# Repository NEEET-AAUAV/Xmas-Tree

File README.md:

# :christmas_tree: :santa: :christmas_tree: DETI X-mas Tree :christmas_tree: :santa: :christmas_tree:

A **simple** (yet rather cool!) Christmas Tree using LEDs and Printed Circuit Boards.

## :gift: List of Material
:snowflake: 64 (or 128) LEDs (_preferably 5mm LEDs_)  
:snowflake: 1 Arduino Nano  
:snowflake: 24 BC557  
:snowflake: 4 JHC138 (or 74HCT138)  
:snowflake: SMD Resistors  
:snowflake: Double Layer Printed Circuit Boards  

## :triangular_ruler: Tree Dimensions
:snowflake:  Approximately an A4 paper sheet

## What we did...
:snowflake: [Arduino Code](Xmas_tree.ino/)  
:snowflake: [Schematic & Board](PCB)  
:snowflake: 3D printed parts: [The Original](https://www.thingiverse.com/thing:537944) and [Our version](https://github.com/NEEET-AAUAV/Xmas-Tree/tree/master/Support)

## How we did it?
The projected electrical circuit is similar to a LED matrix, allowing only one LED ON at any given time.   
To create the illusion of multiple LEDs on, the control algorithm toggles the desired LEDs, one by one, through the decoder hardware at a high frequency, therefore creating the illusion of multiple LEDs being on at the same time.  
A decoder IC is required to control the LEDs independently, enabling the creation of multiple and elaborated animation schemes.  

## Authors
:santa: [André Gradim](https://github.com/a-gradim)  
:santa: [Pedro Martins](https://github.com/k3rn3l-pan1c)  

### Other Elfs worth mention
:snowman: [Hugo Leal](https://github.com/HugoLeal)  
:snowman: [Beatriz Silva](https://github.com/b-dsilva)

--- 

Wanna get in contact?  
Reach us by email: neeetua@gmail.com

---

Created By [NEEET - Núcleo de Estudantes de Eletrónica e Telecomunicações](https://www.facebook.com/neeetaauav/)  
[Department of Electronics, Telecommunications and Informatics](https://www.ua.pt/deti/)  
[University of Aveiro](https://www.ua.pt/)

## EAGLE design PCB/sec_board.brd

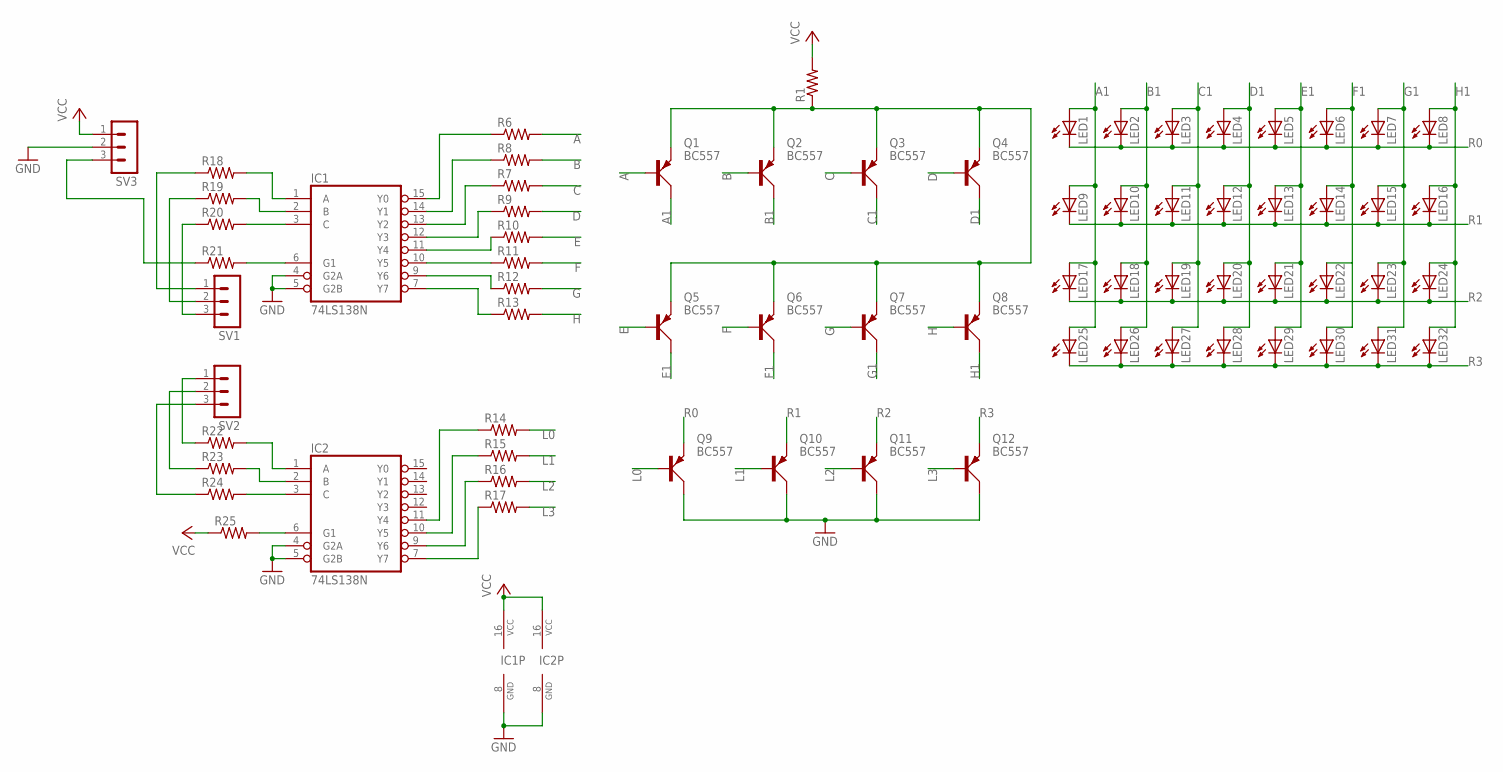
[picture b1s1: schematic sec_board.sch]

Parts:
IC1, IC2: 74LS138N; DIL16
LED1, LED2, LED3, LED4, LED5, LED6, LED7, LED8, LED9, LED10, LED11, LED12, LED13, LED14, LED15, LED16, LED17, LED18, LED19, LED20, LED21, LED22, LED23, LED24, LED25, LED26, LED27, LED28, LED29, LED30, LED31, LED32: LED5MM
Q1, Q2, Q3, Q4, Q5, Q6, Q7, Q8, Q9, Q10, Q11, Q12: BC557; SOT54A
R1, R6, R7, R8, R9, R10, R11, R12, R13, R14, R15, R16, R17: R-US_R0805; R0805
R18, R19, R20, R21, R22, R23, R24, R25: R-US_M0805; M0805
SV1, SV2, SV3: MA03-1

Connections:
A: Q1.B, R6.2
A1: LED1.A, LED9.A, LED17.A, LED25.A, Q1.C
B: Q2.B, R8.2
B1: LED2.A, LED10.A, LED18.A, LED26.A, Q2.C
C: Q3.B, R7.2
C1: LED3.A, LED11.A, LED19.A, LED27.A, Q3.C
D: Q4.B, R9.2
D1: LED4.A, LED12.A, LED20.A, LED28.A, Q4.C
E: Q5.B, R10.2
E1: LED5.A, LED13.A, LED21.A, LED29.A, Q5.C
F: Q6.B, R11.2
F1: LED6.A, LED14.A, LED22.A, LED30.A, Q6.C
G: Q7.B, R12.2
G1: LED7.A, LED15.A, LED23.A, LED31.A, Q7.C
GND: IC1.4 (G2A), IC1.5 (G2B), IC1.8 (GND), IC2.4 (G2A), IC2.5 (G2B), IC2.8 (GND), Q9.C, Q10.C, Q11.C, Q12.C, SV3.2
H: Q8.B, R13.2
H1: LED8.A, LED16.A, LED24.A, LED32.A, Q8.C
L0: Q9.B, R14.2
L1: Q10.B, R15.2
L2: Q11.B, R16.2
L3: Q12.B, R17.2
unnamed: IC2.7 (Y7), R17.1
unnamed: IC1.15 (Y0), R6.1
unnamed: IC1.14 (Y1), R8.1
unnamed: IC2.9 (Y6), R16.1
unnamed: IC1.13 (Y2), R7.1
unnamed: IC1.12 (Y3), R9.1
unnamed: IC1.11 (Y4), R10.1
unnamed: IC1.10 (Y5), R11.1
unnamed: IC1.9 (Y6), R12.1
unnamed: IC1.7 (Y7), R13.1
unnamed: IC2.10 (Y5), R15.1
unnamed: IC2.11 (Y4), R14.1
unnamed: Q1.E, Q2.E, Q3.E, Q4.E, Q5.E, Q6.E, Q7.E, Q8.E, R1.1
unnamed: R24.1, SV2.3
unnamed: R23.1, SV2.2
unnamed: R22.1, SV2.1
unnamed: R20.1, SV1.3
unnamed: R19.1, SV1.2
unnamed: R18.1, SV1.1
unnamed: R21.1, SV3.3
unnamed: IC2.3 (C), R24.2
unnamed: IC2.2 (B), R23.2
unnamed: IC2.1 (A), R22.2
unnamed: IC1.3 (C), R20.2
unnamed: IC1.2 (B), R19.2
unnamed: IC1.1 (A), R18.2
unnamed: IC1.6 (G1), R21.2
unnamed: IC2.6 (G1), R25.2
R0: LED1.K (C), LED2.K (C), LED3.K (C), LED4.K (C), LED5.K (C), LED6.K (C), LED7.K (C), LED8.K (C), Q9.E
R1: LED9.K (C), LED10.K (C), LED11.K (C), LED12.K (C), LED13.K (C), LED14.K (C), LED15.K (C), LED16.K (C), Q10.E
R2: LED17.K (C), LED18.K (C), LED19.K (C), LED20.K (C), LED21.K (C), LED22.K (C), LED23.K (C), LED24.K (C), Q11.E
R3: LED25.K (C), LED26.K (C), LED27.K (C), LED28.K (C), LED29.K (C), LED30.K (C), LED31.K (C), LED32.K (C), Q12.E
VCC: IC1.16 (VCC), IC2.16 (VCC), R1.2, R25.1, SV3.1

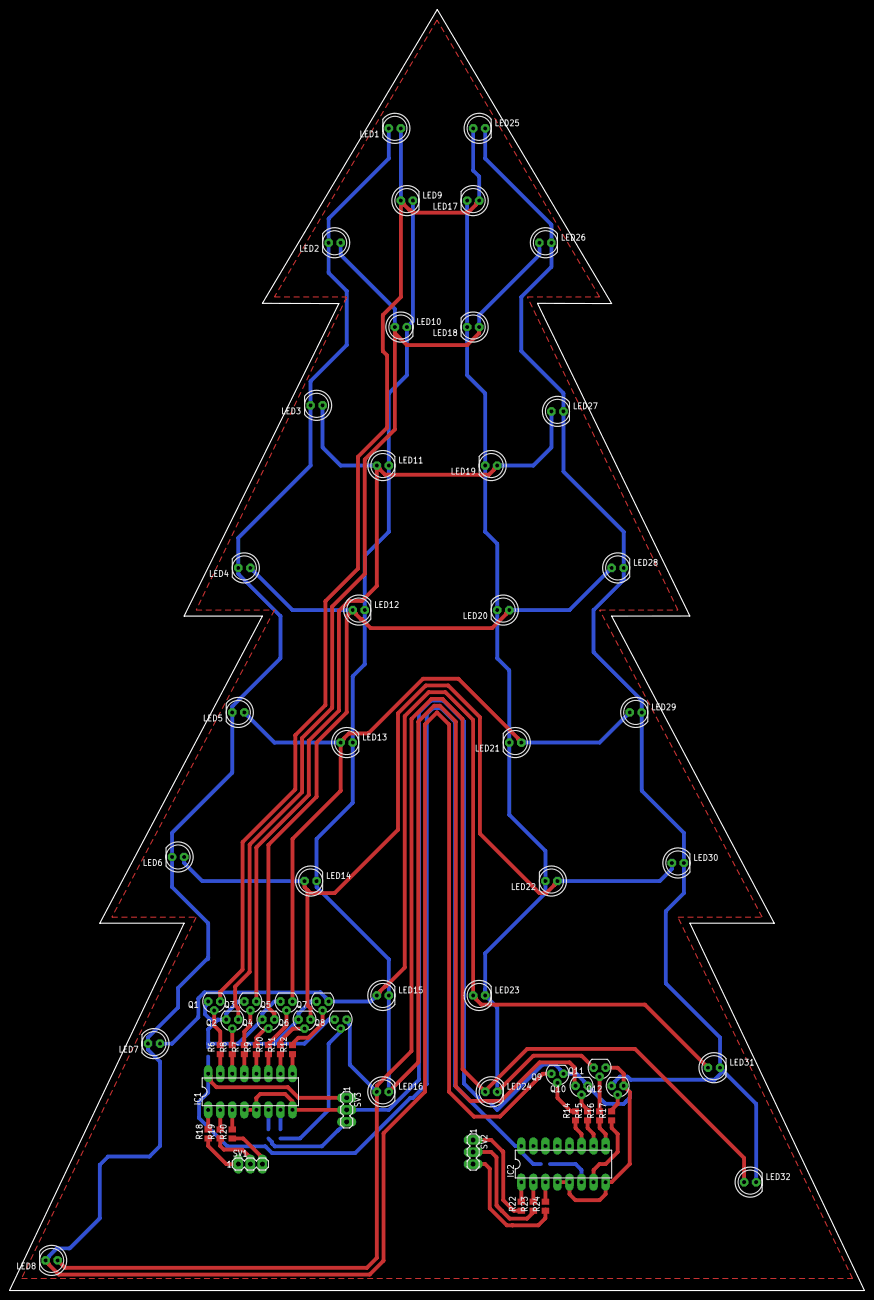
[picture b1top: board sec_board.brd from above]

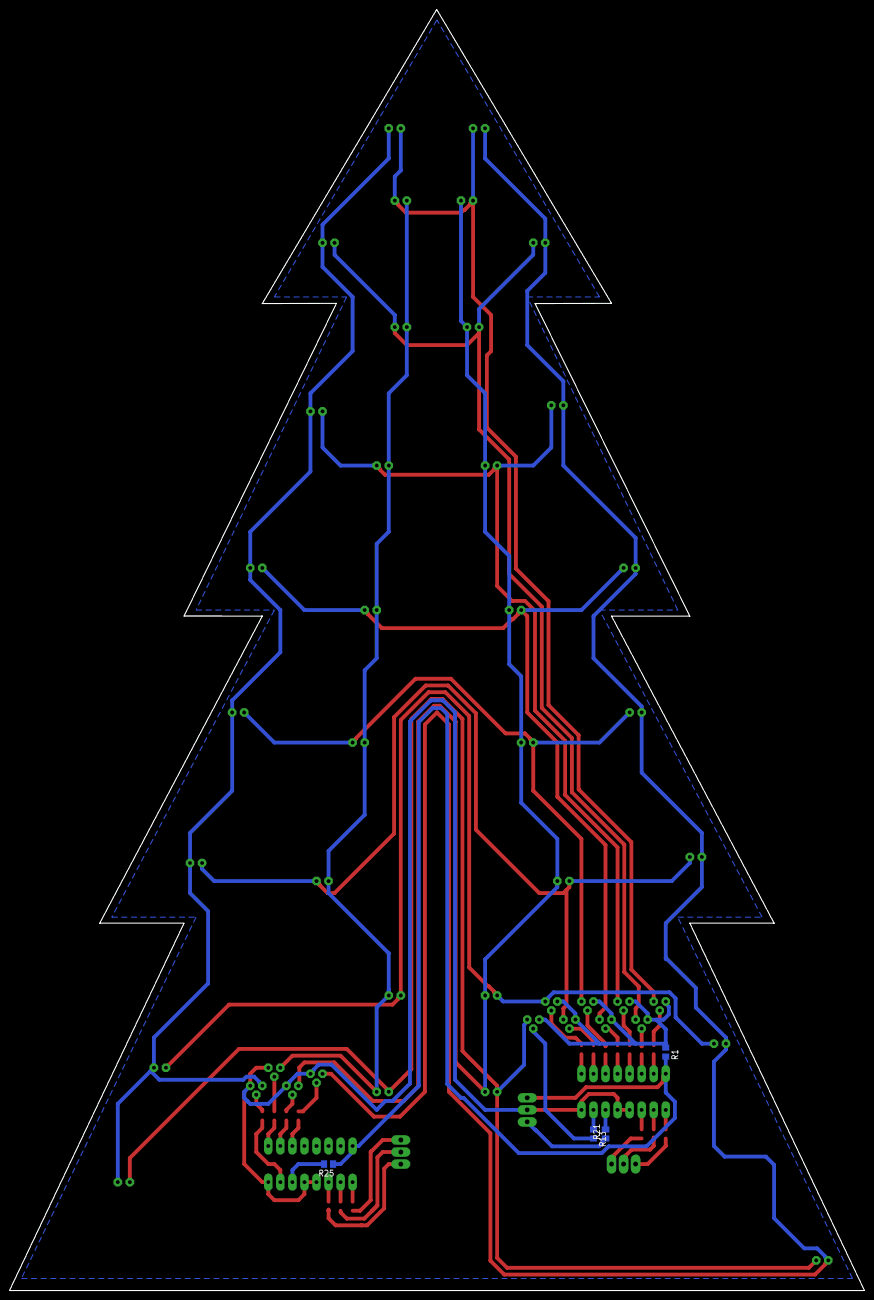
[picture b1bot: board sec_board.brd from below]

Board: 2 copper layers, 180.3 x 270.2 mm, 70 parts (4 on the bottom side), 54 nets.

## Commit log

2017-12-24 [WIP] Added Readme
2017-12-24 Final version of the Arduino Code
2017-12-24 [WIP] Updated General Readme
2017-12-24 [WIP] Added Authors to Readme
2017-12-24 [WIP] Fixed Typos
2017-12-24 Final General README
2017-12-24 [WIP] Small Code Documentation
2017-12-24 [WIP] Fixed typos & Update README.md
2017-12-24 Minor corrections to README
2017-12-24 PCB - Schematic and board
2017-12-24 Update time constants documentation in README
2017-12-29 Added support stl
2018-07-24 A forgotten Summer commit
2018-07-24 Added Gitignore
